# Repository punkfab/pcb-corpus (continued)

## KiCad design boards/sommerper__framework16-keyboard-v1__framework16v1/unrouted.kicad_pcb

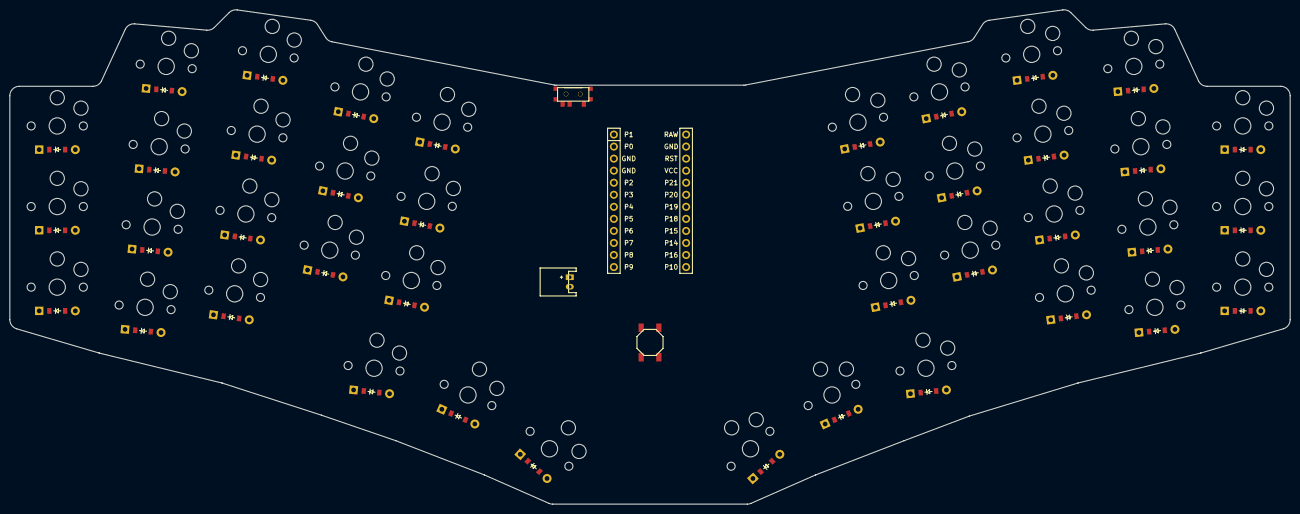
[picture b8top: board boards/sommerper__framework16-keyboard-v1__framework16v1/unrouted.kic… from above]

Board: 2 copper layers, 270.0 x 104.2 mm, 84 parts (0 on the bottom side), 58 nets, no tracks yet.

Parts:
B1: SW_TACT_ALPS_SKQGABE010
D1, D2, D3, D4, D5, D6, D7, D8, D9, D10, D11, D12, D13, D14, D15, D16, D17, D18, D19, D20, D21, D22, D23, D24, D25, D26, D27, D28, D29, D30, D31, D32, D33, D34, D35, D36, D37, D38, D39, D40: ComboDiode
JST1: JST_PH_S2B-PH-K_02x2.00mm_Angled
MCU1: mcu_supermini_nrf52840
S1, S2, S3, S4, S5, S6, S7, S8, S9, S10, S11, S12, S13, S14, S15, S16, S17, S18, S19, S20, S21, S22, S23, S24, S25, S26, S27, S28, S29, S30, S31, S32, S33, S34, S35, S36, S37, S38, S39, S40: PG1350
T1: SPDT_C128955

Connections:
BAT: JST1.1, T1.2
GND: B1.1, JST1.2, MCU1.2, MCU1.21, MCU1.22
P0: D2.1, D6.1, D10.1, D13.1, D16.1, MCU1.23
P1: D3.1, D7.1, D11.1, D14.1, D17.1, MCU1.24
P4: D1.1, D5.1, D9.1, D12.1, D15.1, MCU1.18
P5: D4.1, D8.1, D18.1, D19.1, D20.1, MCU1.17
P7: MCU1.15, S1.1, S2.1, S3.1, S21.1, S22.1, S23.1
P8: MCU1.14, S4.1, S5.1, S6.1, S7.1, S24.1, S25.1, S26.1, S27.1
P9: MCU1.13, S8.1, S9.1, S10.1, S11.1, S28.1, S29.1, S30.1, S31.1
P10: MCU1.12, S12.1, S13.1, S14.1, S18.1, S32.1, S33.1, S34.1, S38.1
P15: MCU1.9, S20.1, S40.1
P16: MCU1.11, S15.1, S16.1, S17.1, S19.1, S35.1, S36.1, S37.1, S39.1
P18: D24.1, D28.1, D38.1, D39.1, D40.1, MCU1.8
P19: D21.1, D25.1, D29.1, D32.1, D35.1, MCU1.7
P20: D22.1, D26.1, D30.1, D33.1, D36.1, MCU1.6
P21: D23.1, D27.1, D31.1, D34.1, D37.1, MCU1.5
RAW: MCU1.1, T1.1
RST: B1.2, MCU1.3
far_thumb: D20.2, S20.2
home_thumb: D19.2, S19.2
index_home: D12.2, S12.2
index_num: D14.2, S14.2
index_top: D13.2, S13.2
inner_home: D15.2, S15.2
inner_num: D17.2, S17.2
inner_top: D16.2, S16.2
middle_bottom: D8.2, S8.2
middle_home: D9.2, S9.2
middle_num: D11.2, S11.2
middle_top: D10.2, S10.2
mirror_far_thumb: D40.2, S40.2
mirror_home_thumb: D39.2, S39.2
mirror_index_home: D32.2, S32.2
mirror_index_num: D34.2, S34.2
mirror_index_top: D33.2, S33.2
mirror_inner_home: D35.2, S35.2
mirror_inner_num: D37.2, S37.2
mirror_inner_top: D36.2, S36.2
mirror_middle_bottom: D28.2, S28.2
mirror_middle_home: D29.2, S29.2
mirror_middle_num: D31.2, S31.2
mirror_middle_top: D30.2, S30.2
mirror_near_thumb: D38.2, S38.2
mirror_pinky_home: D21.2, S21.2
mirror_pinky_num: D23.2, S23.2
mirror_pinky_top: D22.2, S22.2
mirror_ring_bottom: D24.2, S24.2
mirror_ring_home: D25.2, S25.2
mirror_ring_num: D27.2, S27.2
mirror_ring_top: D26.2, S26.2
near_thumb: D18.2, S18.2
pinky_home: D1.2, S1.2
pinky_num: D3.2, S3.2
pinky_top: D2.2, S2.2
ring_bottom: D4.2, S4.2
ring_home: D5.2, S5.2
ring_num: D7.2, S7.2
ring_top: D6.2, S6.2
